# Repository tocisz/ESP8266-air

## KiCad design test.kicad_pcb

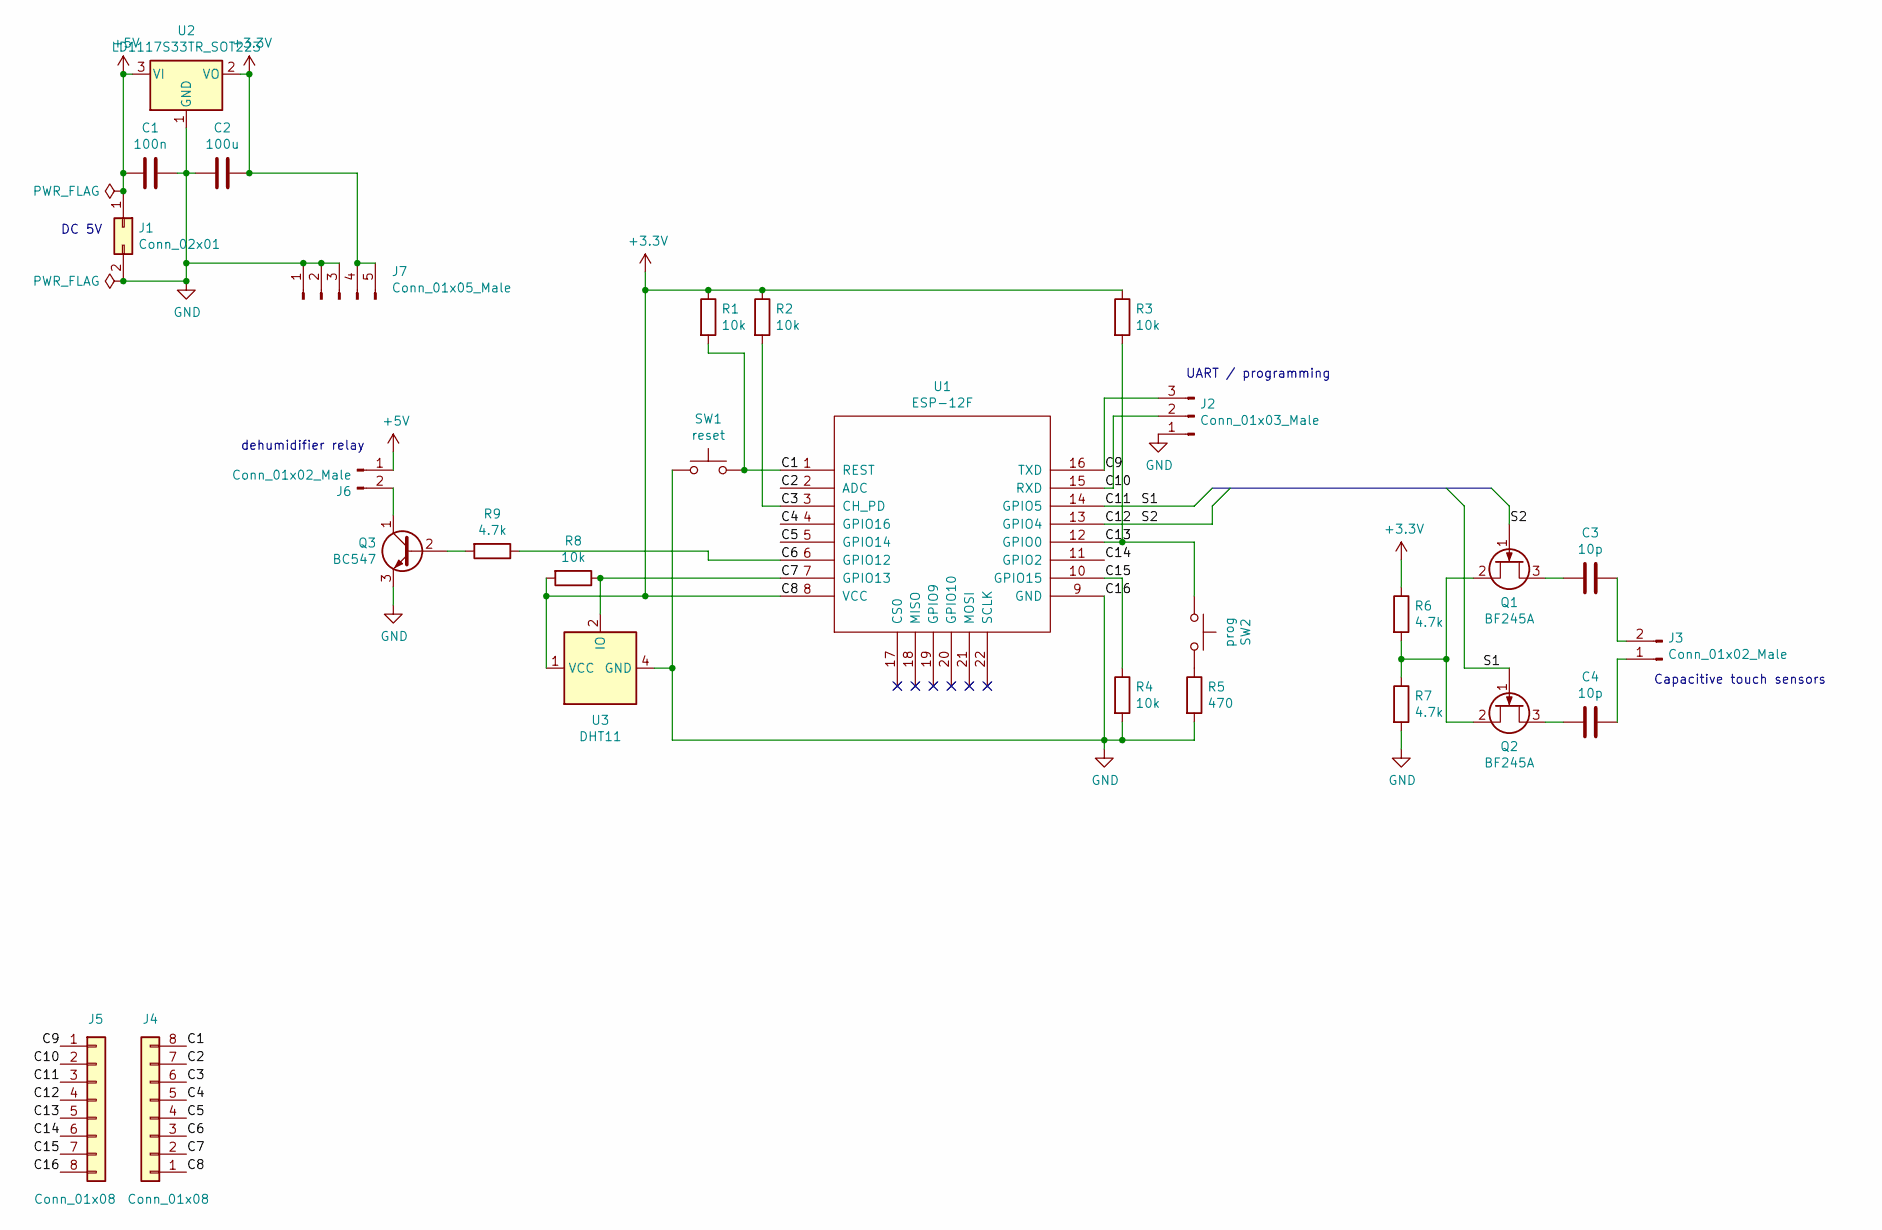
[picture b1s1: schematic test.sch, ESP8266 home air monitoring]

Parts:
C1: 100n; C_Disc_D5.0mm_W2.5mm_P2.50mm
C2: 100u; CP_Radial_D6.3mm_P2.50mm
C3, C4: 10p; C_Disc_D5.0mm_W2.5mm_P2.50mm
J1: Conn_02x01; SolderWirePad_1x02_P5.08mm_Drill1.5mm
J2: Conn_01x03_Male; PinHeader_1x03_P2.54mm_Vertical
J3, J6: Conn_01x02_Male; PinHeader_1x02_P2.54mm_Horizontal
J4, J5: Conn_01x08; PinSocket_1x08_P2.54mm_Vertical
J7: Conn_01x05_Male; PinHeader_1x05_P2.54mm_Horizontal
Q1, Q2: BF245A; TO-92_Inline_Wide
Q3: BC547; TO-92_Inline
R1, R2, R3, R4: 10k; R_Axial_DIN0207_L6.3mm_D2.5mm_P10.16mm_Horizontal
R5: 470; R_Axial_DIN0207_L6.3mm_D2.5mm_P10.16mm_Horizontal
R6, R7, R9: 4.7k; R_Axial_DIN0207_L6.3mm_D2.5mm_P10.16mm_Horizontal
R8: 10k; R_Axial_DIN0207_L6.3mm_D2.5mm_P2.54mm_Vertical
SW1: reset; SW_PUSH_6mm_H5mm
SW2: prog; SW_PUSH_6mm_H5mm
U1: ESP-12F; ESP-12E_SMD
U2: LD1117S33TR_SOT223; SOT-223
U3: DHT11; Aosong_DHT11_5.5x12.0_P2.54mm

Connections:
+3V3: C2.1, J4.1, J7.4, J7.5, R1.1, R2.1, R3.1, R6.1, R8.2, U1.8 (VCC), U2.2 (VO), U3.1 (VCC)
+5V: C1.1, J1.1, J6.1, U2.3 (VI)
/C1: J4.8, R1.2, SW1.2, U1.1 (REST)
/C2: J4.7, U1.2 (ADC)
/C3: J4.6, R2.2, U1.3 (CH_PD)
/C4: J4.5, U1.4 (GPIO16)
/C5: J4.4, U1.5 (GPIO14)
/C6: J4.3, R9.1, U1.6 (GPIO12)
/C7: J4.2, R8.1, U1.7 (GPIO13), U3.2 (IO)
/C9: J2.3, J5.1, U1.16 (TXD)
/C10: J2.2, J5.2, U1.15 (RXD)
/C11: J5.3, Q2.1 (G), U1.14 (GPIO5)
/C12: J5.4, Q1.1 (G), U1.13 (GPIO4)
/C13: J5.5, R3.2, SW2.1, U1.12 (GPIO0)
/C14: J5.6, U1.11 (GPIO2)
/C15: J5.7, R4.1, U1.10 (GPIO15)
GND: C1.2, C2.2, J1.2, J2.1, J5.8, J7.1, J7.2, J7.3, Q3.3 (E), R4.2, R5.2, R7.2, SW1.1, U1.9 (GND), U2.1 (GND), U3.4 (GND)
unnamed: C3.1, J3.2
unnamed: C3.2, Q1.3 (D)
unnamed: C4.1, J3.1
unnamed: C4.2, Q2.3 (D)
unnamed: J6.2, Q3.1 (C)
unnamed: Q1.2 (S), Q2.2 (S), R6.2, R7.1
unnamed: Q3.2 (B), R9.2
unnamed: R5.1, SW2.2

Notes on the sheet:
UART / programming
Capacitive touch sensors
dehumidifier relay
DC 5V

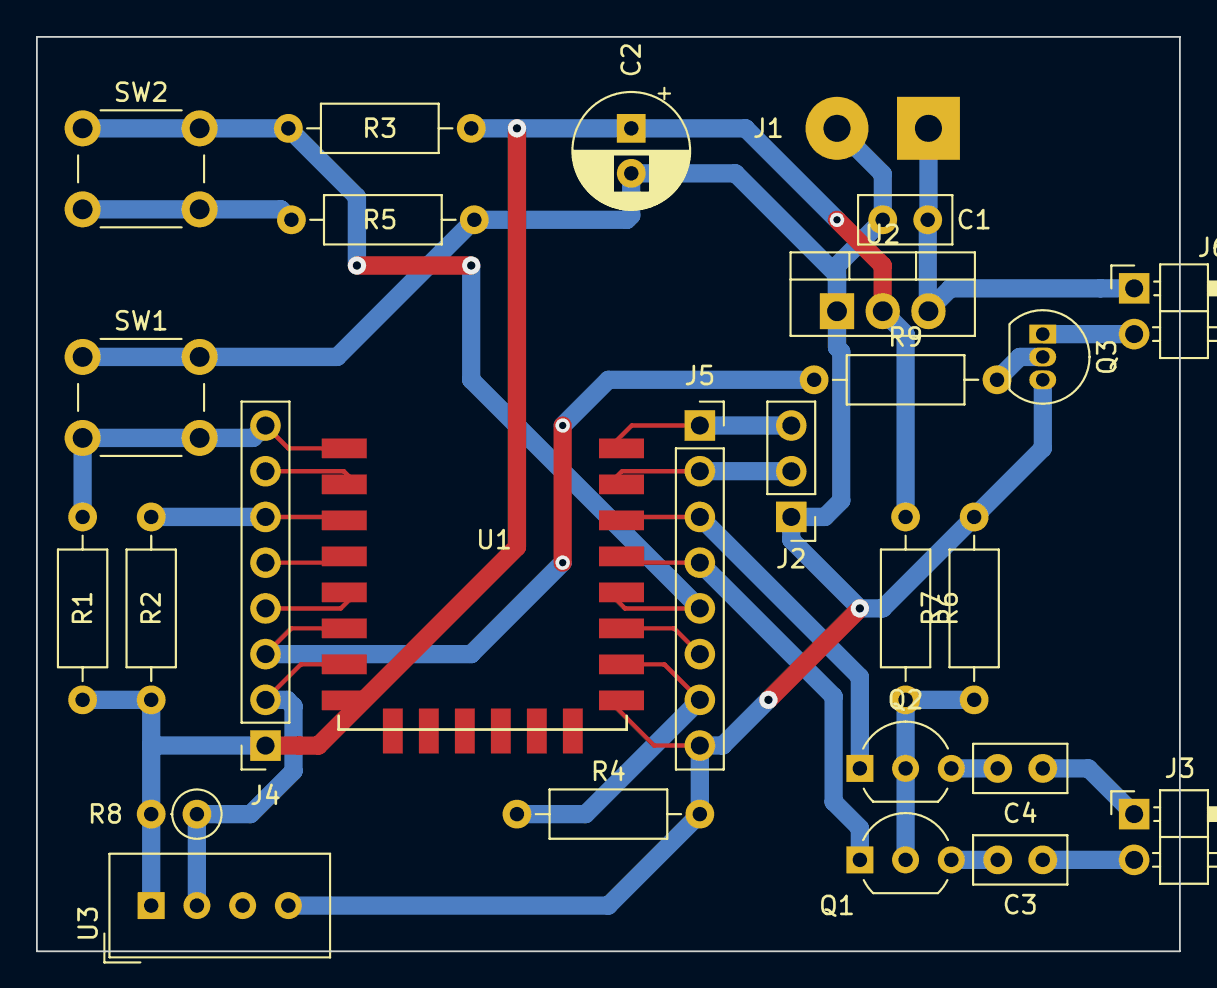
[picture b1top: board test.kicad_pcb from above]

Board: 2 copper layers, 63.5 x 50.8 mm, 27 parts (0 on the bottom side), 25 nets.

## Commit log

2022-03-13 init project
2022-11-02 update library
